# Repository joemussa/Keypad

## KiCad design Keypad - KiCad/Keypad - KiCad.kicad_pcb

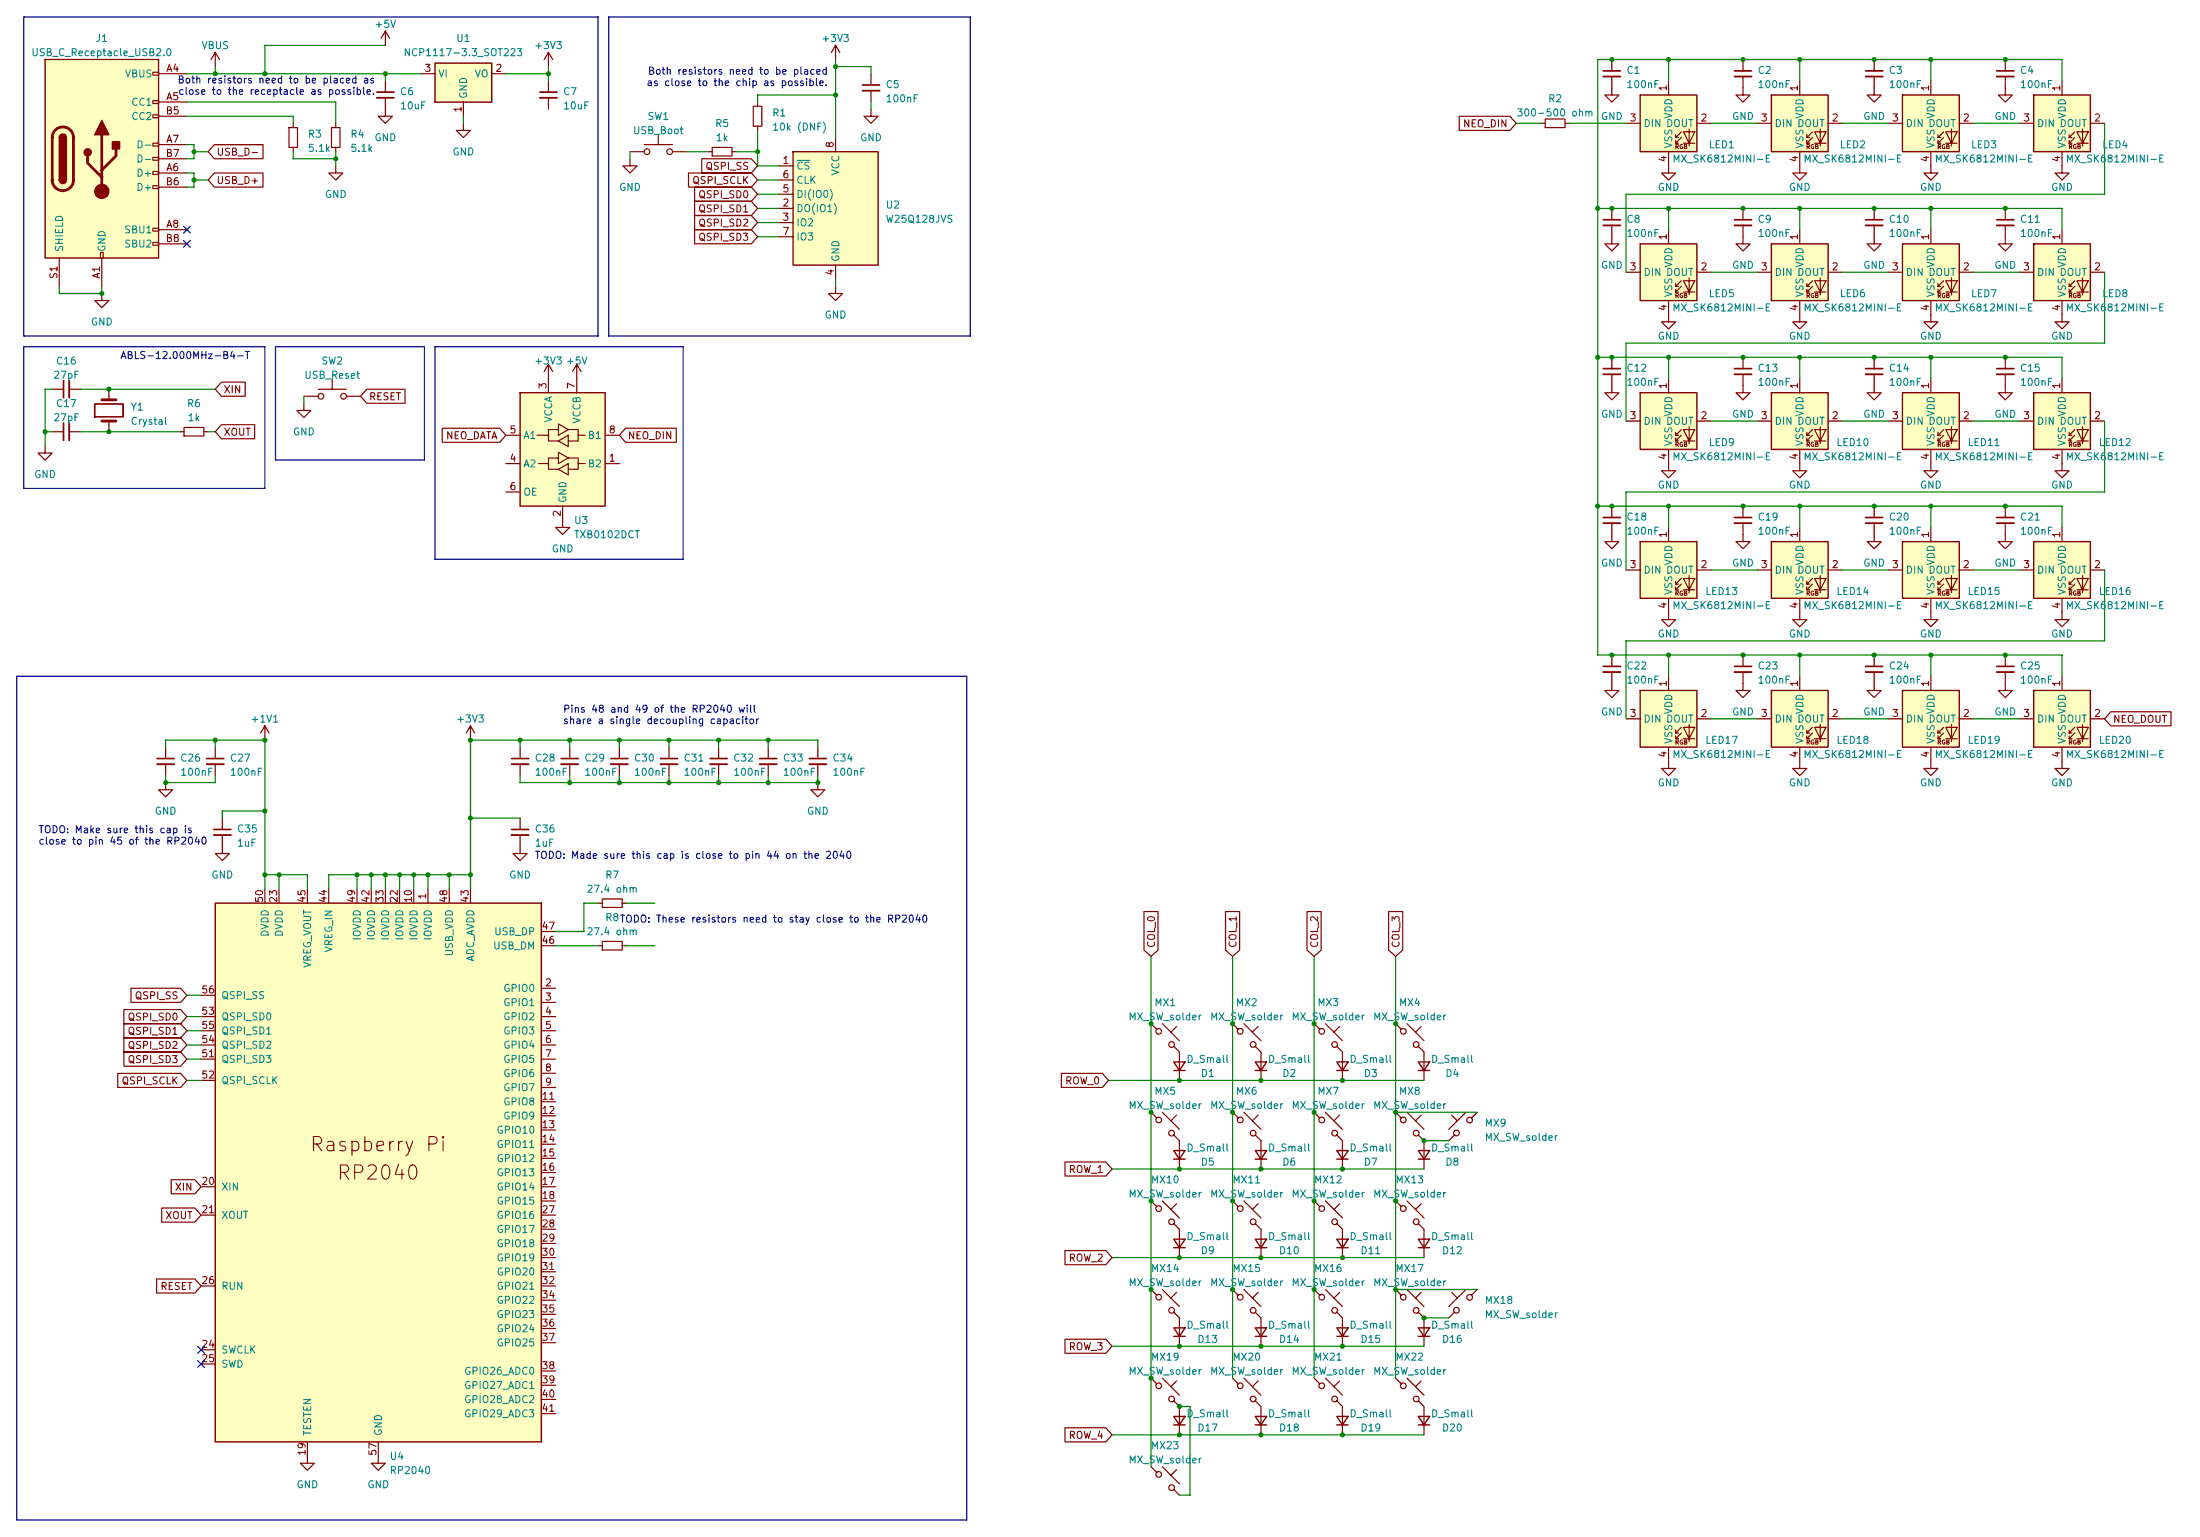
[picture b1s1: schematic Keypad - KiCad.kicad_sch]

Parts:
C1, C2, C3, C4, C5, C8, C9, C10, C11, C12, C13, C14, C15, C18, C19, C20, C21, C22, C23, C24, C25, C26, C27, C28, C29, C30, C31, C32, C33, C34: 100nF; C_0603_1608Metric_Pad1.08x0.95mm_HandSolder
C6, C7: 10uF; C_0603_1608Metric_Pad1.08x0.95mm_HandSolder
C16, C17: 27pF; C_0603_1608Metric_Pad1.08x0.95mm_HandSolder
C35, C36: 1uF; C_0603_1608Metric_Pad1.08x0.95mm_HandSolder
D1, D2, D3, D4, D5, D6, D7, D8, D9, D10, D11, D12, D13, D14, D15, D16, D17, D18, D19, D20: D_Small; D_0603_1608Metric_Pad1.05x0.95mm_HandSolder
J1: USB_C_Receptacle_USB2.0; USB_C_Receptacle_GCT_USB4085
LED1, LED2, LED3, LED4, LED5, LED6, LED7, LED8, LED9, LED10, LED11, LED12, LED13, LED14, LED15, LED16, LED17, LED18, LED19, LED20: MX_SK6812MINI-E; LED_MX_6028R
MX1, MX2, MX3, MX4, MX5, MX6, MX7, MX8, MX9, MX10, MX11, MX12, MX13, MX14, MX15, MX16, MX17, MX18, MX19, MX20, MX21, MX22, MX23: MX_SW_solder; SW_MX_1u
R1: 10k (DNF); R_0603_1608Metric_Pad0.98x0.95mm_HandSolder
R2: 300-500 ohm; R_0603_1608Metric_Pad0.98x0.95mm_HandSolder
R3, R4: 5.1k; R_0603_1608Metric_Pad0.98x0.95mm_HandSolder
R5, R6: 1k; R_0603_1608Metric_Pad0.98x0.95mm_HandSolder
R7, R8: 27.4 ohm; R_0603_1608Metric_Pad0.98x0.95mm_HandSolder
SW1: USB_Boot; SW_Push_1P1T_NO_CK_KSC7xxJ
SW2: USB_Reset; SW_Push_1P1T_NO_CK_KSC7xxJ
U1: NCP1117-3.3_SOT223; TO-252-2
U2: W25Q128JVS; SOIC-8_5.23x5.23mm_P1.27mm
U3: TXB0102DCT; TSSOP-8_3x3mm_P0.65mm
U4: RP2040; RP2040-QFN-56
Y1: Crystal; Crystal_HC49-U_Vertical

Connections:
+1V1: C26.1, C27.1, C35.1, U4.23 (DVDD), U4.45 (VREG_VOUT), U4.50 (DVDD)
+3V3: C5.1, C7.1, C28.1, C29.1, C30.1, C31.1, C32.1, C33.1, C34.1, C36.1, R1.1, U1.2 (VO), U2.8 (VCC), U3.3 (VCCA), U4.1 (IOVDD), U4.10 (IOVDD), U4.22 (IOVDD), U4.33 (IOVDD), U4.42 (IOVDD), U4.43 (ADC_AVDD), U4.44 (VREG_IN), U4.48 (USB_VDD), U4.49 (IOVDD)
+5V: C6.1, J1.A4 (VBUS), J1.A9 (VBUS), J1.B4 (VBUS), J1.B9 (VBUS), U1.3 (VI), U3.7 (VCCB)
COL_0: MX1.1, MX5.1, MX10.1, MX14.1, MX19.1, MX23.1
COL_1: MX2.1, MX6.1, MX11.1, MX15.1, MX20.1
COL_2: MX3.1, MX7.1, MX12.1, MX16.1, MX21.1
COL_3: MX4.1, MX8.1, MX9.2, MX13.1, MX17.1, MX18.2, MX22.1
GND: C1.2, C2.2, C3.2, C4.2, C5.2, C6.2, C8.2, C9.2, C10.2, C11.2, C12.2, C13.2, C14.2, C15.2, C16.1, C17.1, C18.2, C19.2, C20.2, C21.2, C22.2, C23.2, C24.2, C25.2, C26.2, C27.2, C28.2, C29.2, C30.2, C31.2, C32.2, C33.2, C34.2, C35.2, C36.2, J1.A1 (GND), J1.A12 (GND), J1.B1 (GND), J1.B12 (GND), J1.S1 (SHIELD), LED1.4 (VSS), LED2.4 (VSS), LED3.4 (VSS), LED4.4 (VSS), LED5.4 (VSS), LED6.4 (VSS), LED7.4 (VSS), LED8.4 (VSS), LED9.4 (VSS), LED10.4 (VSS), LED11.4 (VSS), LED12.4 (VSS), LED13.4 (VSS), LED14.4 (VSS), LED15.4 (VSS), LED16.4 (VSS), LED17.4 (VSS), LED18.4 (VSS), LED19.4 (VSS), LED20.4 (VSS), R3.2, R4.2, SW1.1, SW2.1, U1.1 (GND), U2.4 (GND), U3.2 (GND), U4.19 (TESTEN), U4.57 (GND)
NEO_DATA: U3.5 (A1)
NEO_DIN: R2.1, U3.8 (B1)
NEO_DOUT: LED20.2 (DOUT)
unnamed: C17.2, R6.1, Y1.1
unnamed: D1.2 (A), MX1.2
unnamed: D2.2 (A), MX2.2
unnamed: D3.2 (A), MX3.2
unnamed: D4.2 (A), MX4.2
unnamed: D5.2 (A), MX5.2
unnamed: D6.2 (A), MX6.2
unnamed: D7.2 (A), MX7.2
unnamed: D8.2 (A), MX8.2, MX9.1
unnamed: D9.2 (A), MX10.2
unnamed: D10.2 (A), MX11.2
unnamed: D11.2 (A), MX12.2
unnamed: D12.2 (A), MX13.2
unnamed: D13.2 (A), MX14.2
unnamed: D14.2 (A), MX15.2
unnamed: D15.2 (A), MX16.2
unnamed: D16.2 (A), MX17.2, MX18.1
unnamed: D17.2 (A), MX19.2, MX23.2
unnamed: D18.2 (A), MX20.2
unnamed: D19.2 (A), MX21.2
unnamed: D20.2 (A), MX22.2
unnamed: J1.A5 (CC1), R4.1
unnamed: J1.B5 (CC2), R3.1
unnamed: LED1.3 (DIN), R2.2
unnamed: LED1.2 (DOUT), LED2.3 (DIN)
unnamed: C1.1, C2.1, C3.1, C4.1, C8.1, C9.1, C10.1, C11.1, C12.1, C13.1, C14.1, C15.1, C18.1, C19.1, C20.1, C21.1, C22.1, C23.1, C24.1, C25.1, LED1.1 (VDD), LED2.1 (VDD), LED3.1 (VDD), LED4.1 (VDD), LED5.1 (VDD), LED6.1 (VDD), LED7.1 (VDD), LED8.1 (VDD), LED9.1 (VDD), LED10.1 (VDD), LED11.1 (VDD), LED12.1 (VDD), LED13.1 (VDD), LED14.1 (VDD), LED15.1 (VDD), LED16.1 (VDD), LED17.1 (VDD), LED18.1 (VDD), LED19.1 (VDD), LED20.1 (VDD)
unnamed: LED2.2 (DOUT), LED3.3 (DIN)
unnamed: LED3.2 (DOUT), LED4.3 (DIN)
unnamed: LED4.2 (DOUT), LED5.3 (DIN)
unnamed: LED5.2 (DOUT), LED6.3 (DIN)
unnamed: LED6.2 (DOUT), LED7.3 (DIN)
unnamed: LED7.2 (DOUT), LED8.3 (DIN)
unnamed: LED8.2 (DOUT), LED9.3 (DIN)
unnamed: LED9.2 (DOUT), LED10.3 (DIN)
unnamed: LED10.2 (DOUT), LED11.3 (DIN)
unnamed: LED11.2 (DOUT), LED12.3 (DIN)
unnamed: LED12.2 (DOUT), LED13.3 (DIN)
unnamed: LED13.2 (DOUT), LED14.3 (DIN)
unnamed: LED14.2 (DOUT), LED15.3 (DIN)
unnamed: LED15.2 (DOUT), LED16.3 (DIN)
unnamed: LED16.2 (DOUT), LED17.3 (DIN)
unnamed: LED17.2 (DOUT), LED18.3 (DIN)
unnamed: LED18.2 (DOUT), LED19.3 (DIN)
unnamed: LED19.2 (DOUT), LED20.3 (DIN)
unnamed: R5.1, SW1.2
unnamed: R8.1, U4.46 (USB_DM)
unnamed: R7.1, U4.47 (USB_DP)
QSPI_SCLK: U2.6 (CLK), U4.52 (QSPI_SCLK)
QSPI_SD0: U2.5 (DI(IO0)), U4.53 (QSPI_SD0)
QSPI_SD1: U2.2 (DO(IO1)), U4.55 (QSPI_SD1)
QSPI_SD2: U2.3 (IO2), U4.54 (QSPI_SD2)
QSPI_SD3: U2.7 (IO3), U4.51 (QSPI_SD3)
QSPI_SS: R1.2, R5.2, U2.1 (~CS), U4.56 (QSPI_SS)
RESET: SW2.2, U4.26 (RUN)
ROW_0: D1.1 (K), D2.1 (K), D3.1 (K), D4.1 (K)
ROW_1: D5.1 (K), D6.1 (K), D7.1 (K), D8.1 (K)
ROW_2: D9.1 (K), D10.1 (K), D11.1 (K), D12.1 (K)
ROW_3: D13.1 (K), D14.1 (K), D15.1 (K), D16.1 (K)
ROW_4: D17.1 (K), D18.1 (K), D19.1 (K), D20.1 (K)
USB_D+: J1.A6 (D+), J1.B6 (D+)
USB_D-: J1.A7 (D-), J1.B7 (D-)
XIN: C16.2, U4.20 (XIN), Y1.2
XOUT: R6.2, U4.21 (XOUT)

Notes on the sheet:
TODO: Made sure this cap is close to pin 44 on the 2040
ABLS-12.000MHz-B4-T
Pins 48 and 49 of the RP2040 will share a single decoupling capacitor
TODO: These resistors need to stay close to the RP2040
TODO: Make sure this cap is close to pin 45 of the RP2040
Both resistors need to be placed as close to the chip as possible.
Both resistors need to be placed as close to the receptacle as possible.

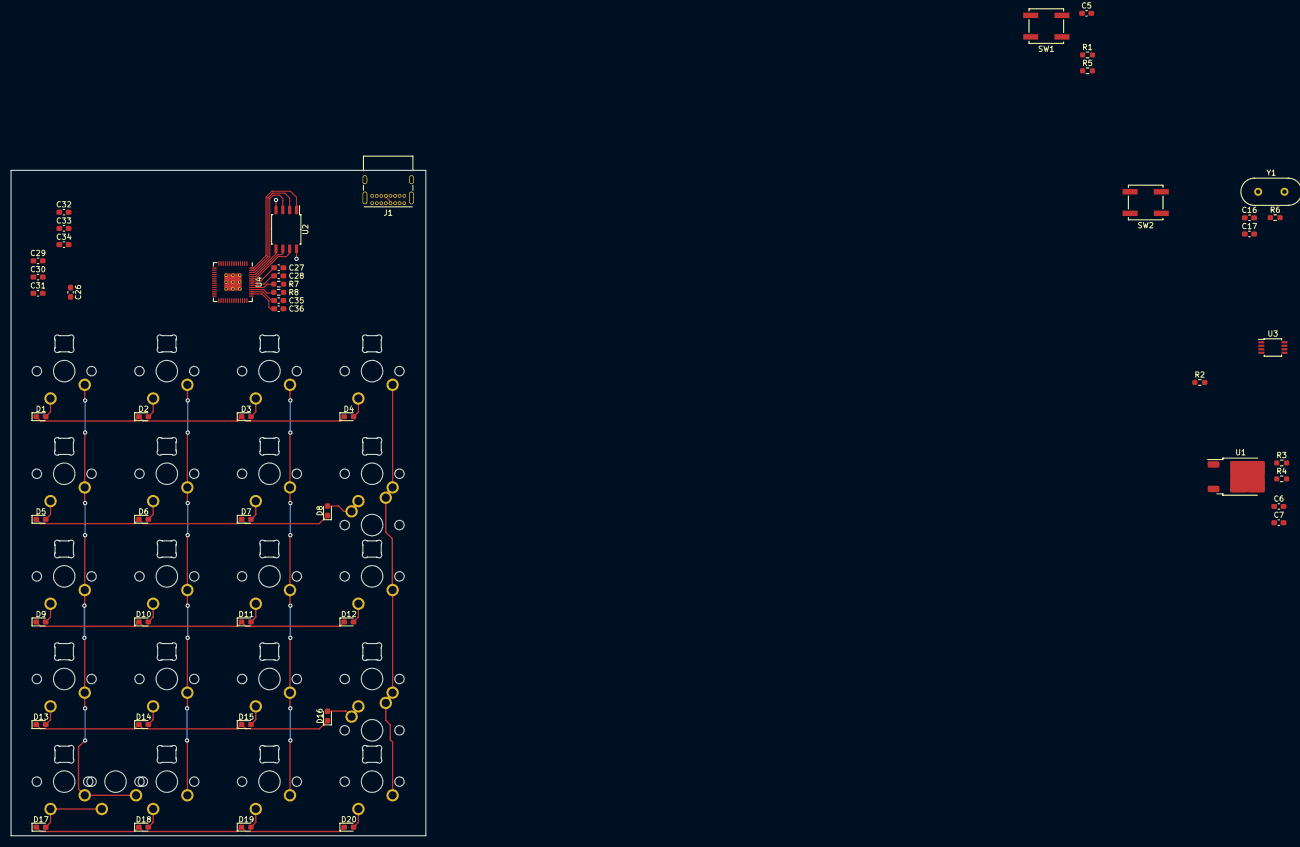
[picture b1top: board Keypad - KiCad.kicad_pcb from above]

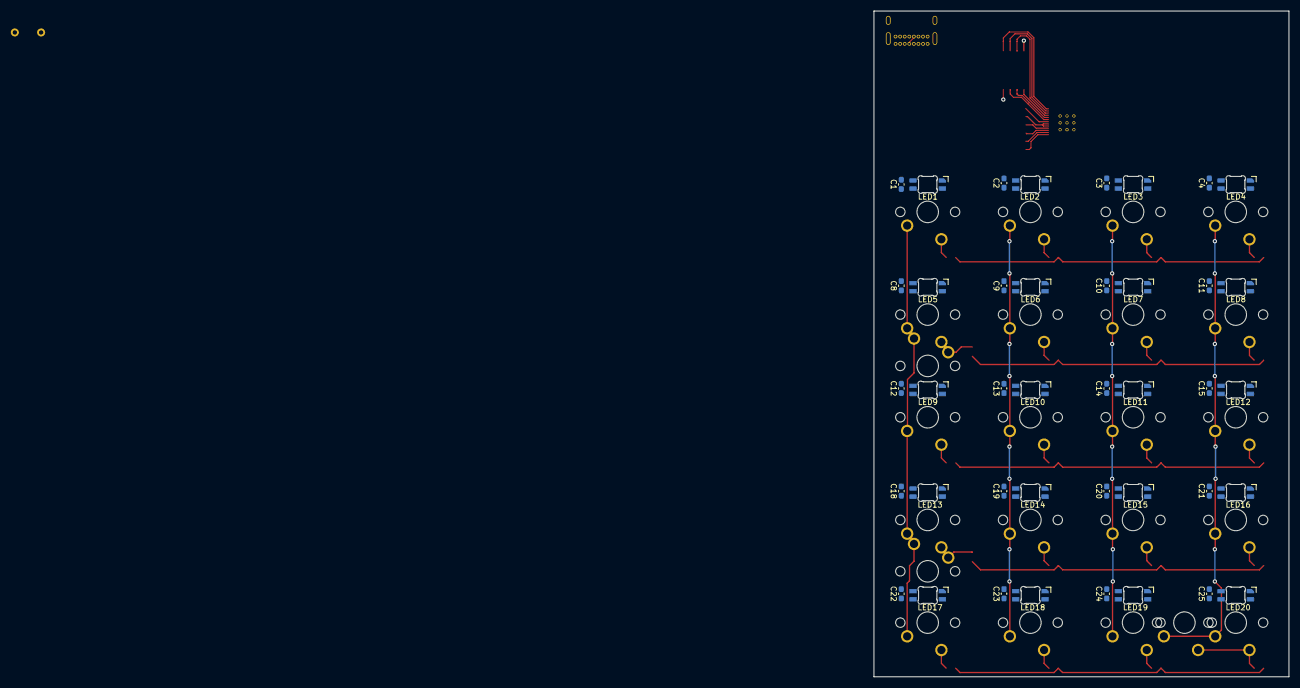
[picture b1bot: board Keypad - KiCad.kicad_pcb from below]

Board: 2 copper layers, 77.0 x 123.5 mm, 115 parts (40 on the bottom side), 72 nets.

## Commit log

2023-04-16 started routing.
    started routing.
